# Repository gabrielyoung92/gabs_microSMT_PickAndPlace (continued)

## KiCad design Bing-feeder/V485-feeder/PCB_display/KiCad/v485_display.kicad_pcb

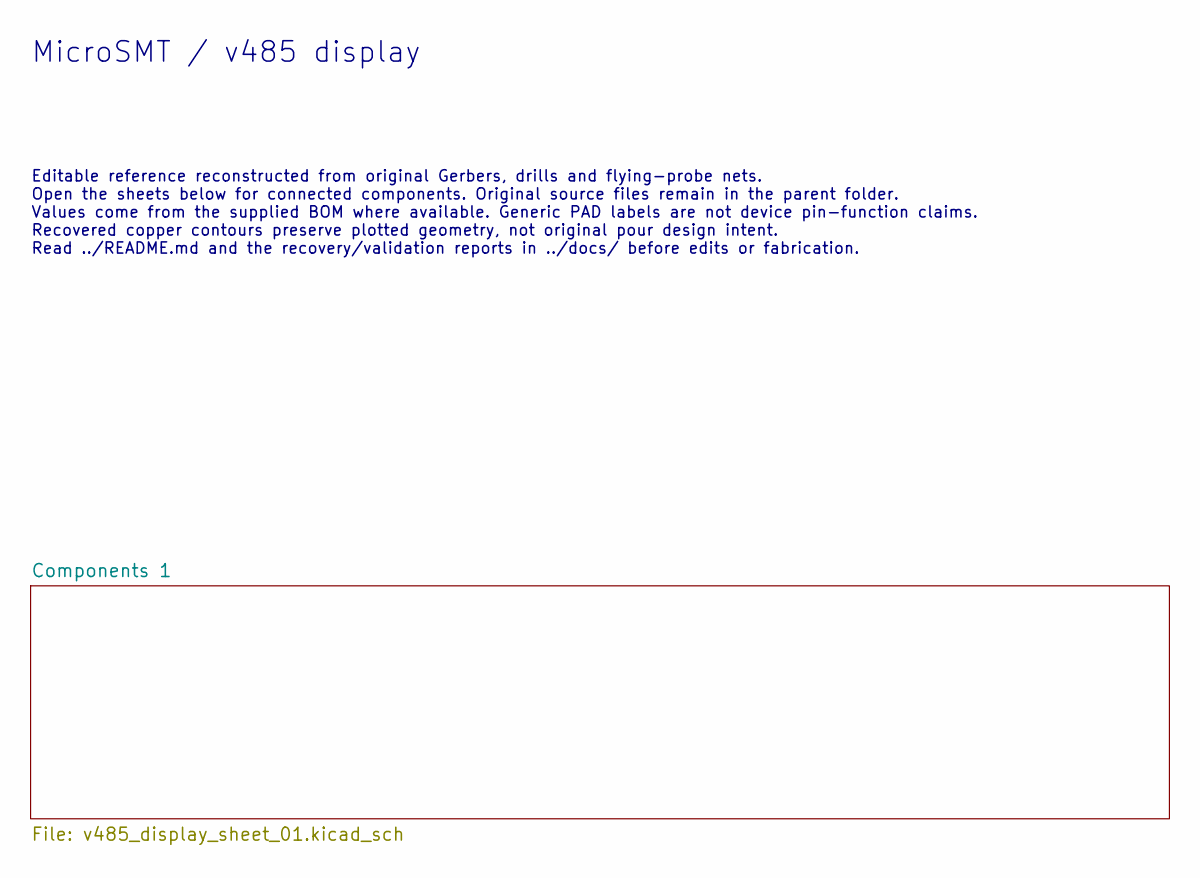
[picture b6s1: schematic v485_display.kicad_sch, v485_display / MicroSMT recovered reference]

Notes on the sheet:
MicroSMT / v485 display
Editable reference reconstructed from original Gerbers, drills and flying-probe nets. Open the sheets below for connected components. Original source files remain in the parent folder. Values come from the supplied BOM where available. Generic PAD labels are not device pin-function claims. Recovere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

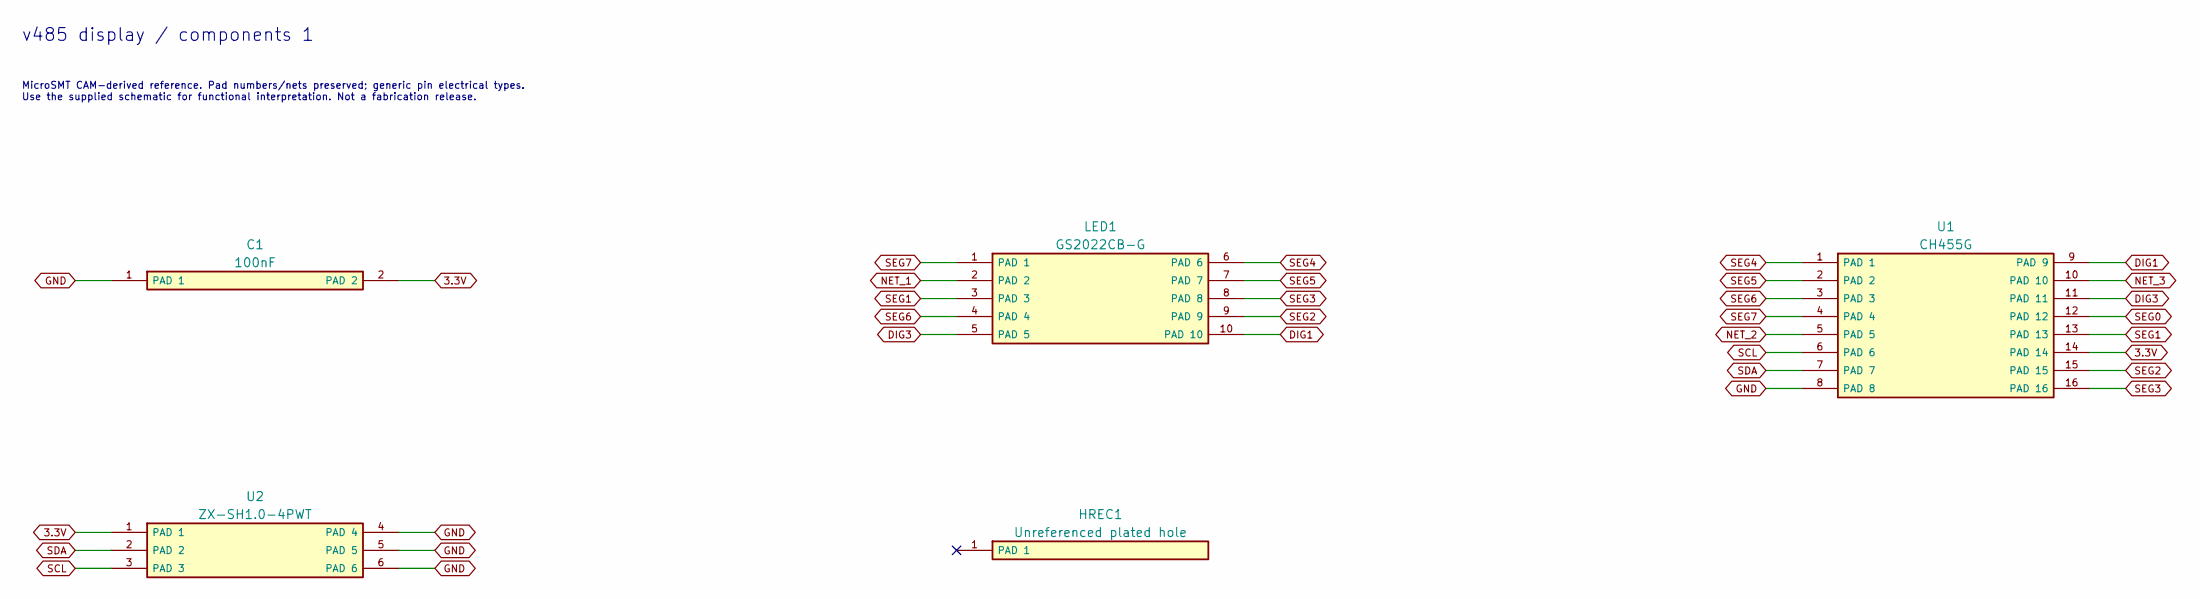
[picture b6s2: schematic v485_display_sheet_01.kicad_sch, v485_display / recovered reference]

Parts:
C1: 100nF; SMD_2_bdaf68bf10
HREC1: Unreferenced plated hole; PTH_1_abea3bc72b
LED1: GS2022CB-G; SMD_10_20c6b414ba
U1: CH455G; SMD_16_61719ae6d4
U2: ZX-SH1.0-4PWT; SMD_6_bf757f6bd6

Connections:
3.3V: C1.2 (PAD 2), U1.14 (PAD 14), U2.1 (PAD 1)
DIG1: LED1.10 (PAD 10), U1.9 (PAD 9)
DIG3: LED1.5 (PAD 5), U1.11 (PAD 11)
GND: C1.1 (PAD 1), U1.8 (PAD 8), U2.4 (PAD 4), U2.5 (PAD 5), U2.6 (PAD 6)
NET_1: LED1.2 (PAD 2)
NET_2: U1.5 (PAD 5)
NET_3: U1.10 (PAD 10)
SCL: U1.6 (PAD 6), U2.3 (PAD 3)
SDA: U1.7 (PAD 7), U2.2 (PAD 2)
SEG0: U1.12 (PAD 12)
SEG1: LED1.3 (PAD 3), U1.13 (PAD 13)
SEG2: LED1.9 (PAD 9), U1.15 (PAD 15)
SEG3: LED1.8 (PAD 8), U1.16 (PAD 16)
SEG4: LED1.6 (PAD 6), U1.1 (PAD 1)
SEG5: LED1.7 (PAD 7), U1.2 (PAD 2)
SEG6: LED1.4 (PAD 4), U1.3 (PAD 3)
SEG7: LED1.1 (PAD 1), U1.4 (PAD 4)

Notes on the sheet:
v485 display / components 1
MicroSMT CAM-derived reference. Pad numbers/nets preserved; generic pin electrical types. Use the supplied schematic for functional interpretation. Not a fabrication release.

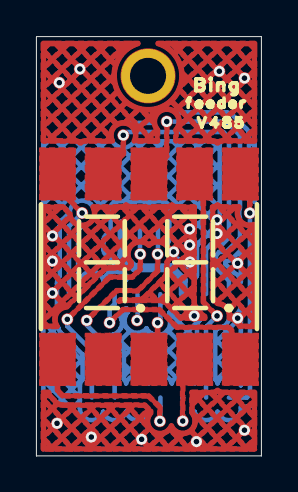
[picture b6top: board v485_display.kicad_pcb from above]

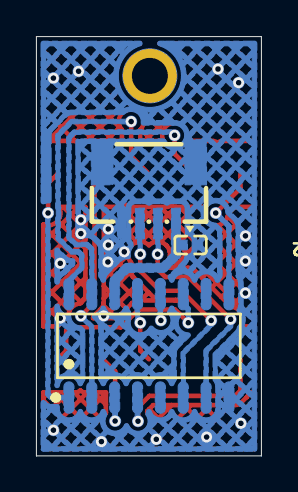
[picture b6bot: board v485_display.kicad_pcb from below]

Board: 2 copper layers, 12.5 x 23.3 mm, 5 parts (3 on the bottom side), 13 nets.

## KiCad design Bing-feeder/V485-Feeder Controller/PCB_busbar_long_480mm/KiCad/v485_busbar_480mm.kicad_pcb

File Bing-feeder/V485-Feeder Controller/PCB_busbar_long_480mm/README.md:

# V485 busbar — 480 mm

> Designs and original files by [MicroSMT](https://github.com/microsmt/Bing-feeder). [Credits and local changes](../../../CREDITS.md).

[Back to collection](../README.md)

Gerbers, editable KiCad files and previews are below.

## KiCad files

Open `.kicad_pro` in **KiCad 10**. Keep the whole `KiCad/` folder together; it contains the local libraries.

The schematics show pad numbers and connections. Use the supplied schematic for pin functions. Review the reported ERC/DRC findings before making a board.

| Project | Open in KiCad | Supporting reports |
| --- | --- | --- |
| V485 480 mm busbar | [v485_busbar_480mm.kicad_pro](KiCad/v485_busbar_480mm.kicad_pro) | [Recovery](docs/recovery.json) · [Validation](docs/validation.json) |

[Recovery details](docs/KICAD_RECOVERY.md) · [Method and editing limits](../../../tools/kicad/RECOVERY_NOTES.md)

## Original board views

[Download Gerber ZIP](Gerber_PCB1_2026-10-09.zip)

<table>
<tr>
<td align="center"><br><sub>Top</sub></td>
<td align="center"><br><sub>Bottom</sub></td>
<td align="center"><br><sub>Top-side isometric</sub></td>
</tr>
</table>

## Assembly notes

MicroSMT specifies **two 480 mm busbars per PNP machine**: one at the front and one at the back.

Gerber previews use display colours and an assumed 1.6 mm thickness; use source data for manufacturing dimensions.

## KiCad previews

KiCad reconstruction views; source Gerber views are above.

### V485 480 mm busbar

<table>
<tr>
<td align="center"><br><sub>Recovered schematic</sub></td>
<td align="center"><br><sub>Recovered PCB top</sub></td>
<td align="center"><br><sub>Recovered PCB bottom</sub></td>
</tr>
</table>

[Sheet overview](photos/kicad-v485_busbar_480mm-overview.jpg) · [Components 1](photos/kicad-v485_busbar_480mm-sheet-01.jpg)

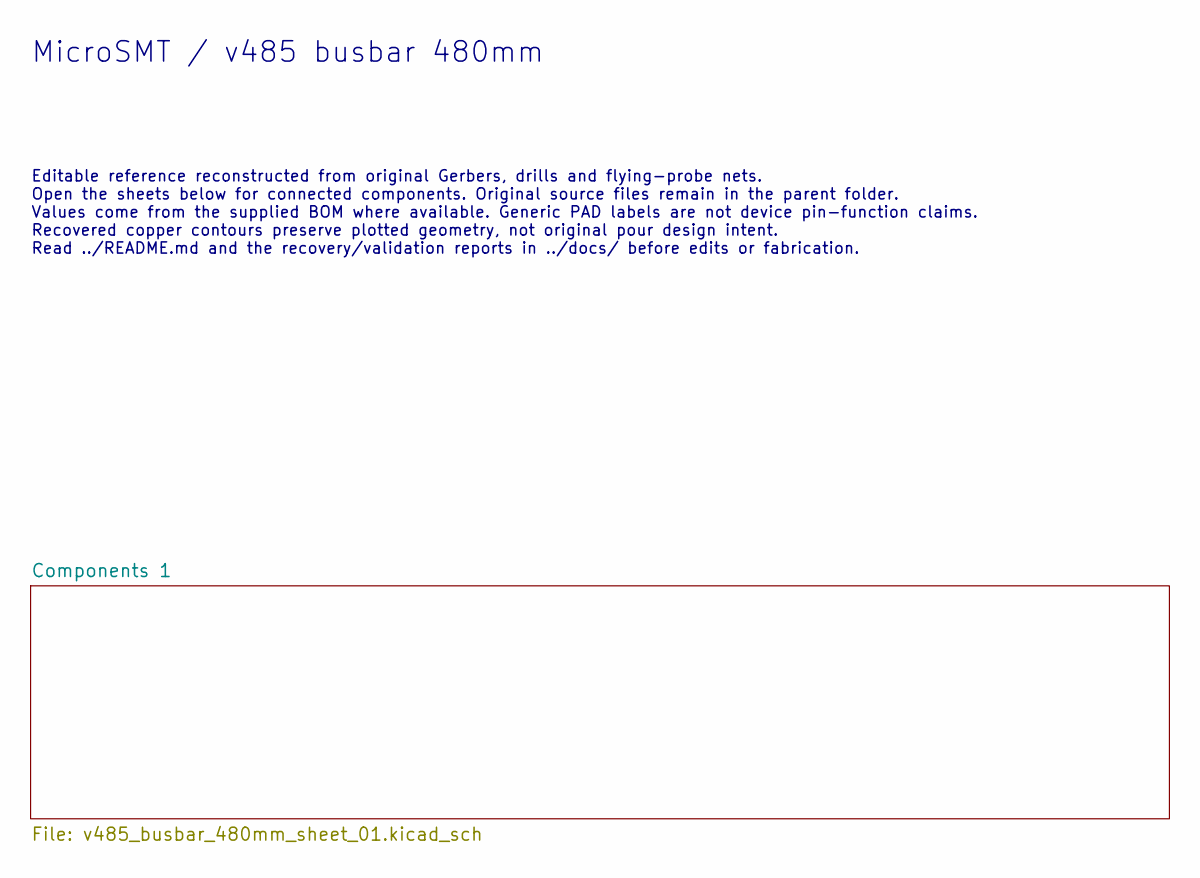
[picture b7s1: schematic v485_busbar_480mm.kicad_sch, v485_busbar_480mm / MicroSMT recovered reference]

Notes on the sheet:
MicroSMT / v485 busbar 480mm
Editable reference reconstructed from original Gerbers, drills and flying-probe nets. Open the sheets below for connected components. Original source files remain in the parent folder. Values come from the supplied BOM where available. Generic PAD labels are not device pin-function claims. Recovere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

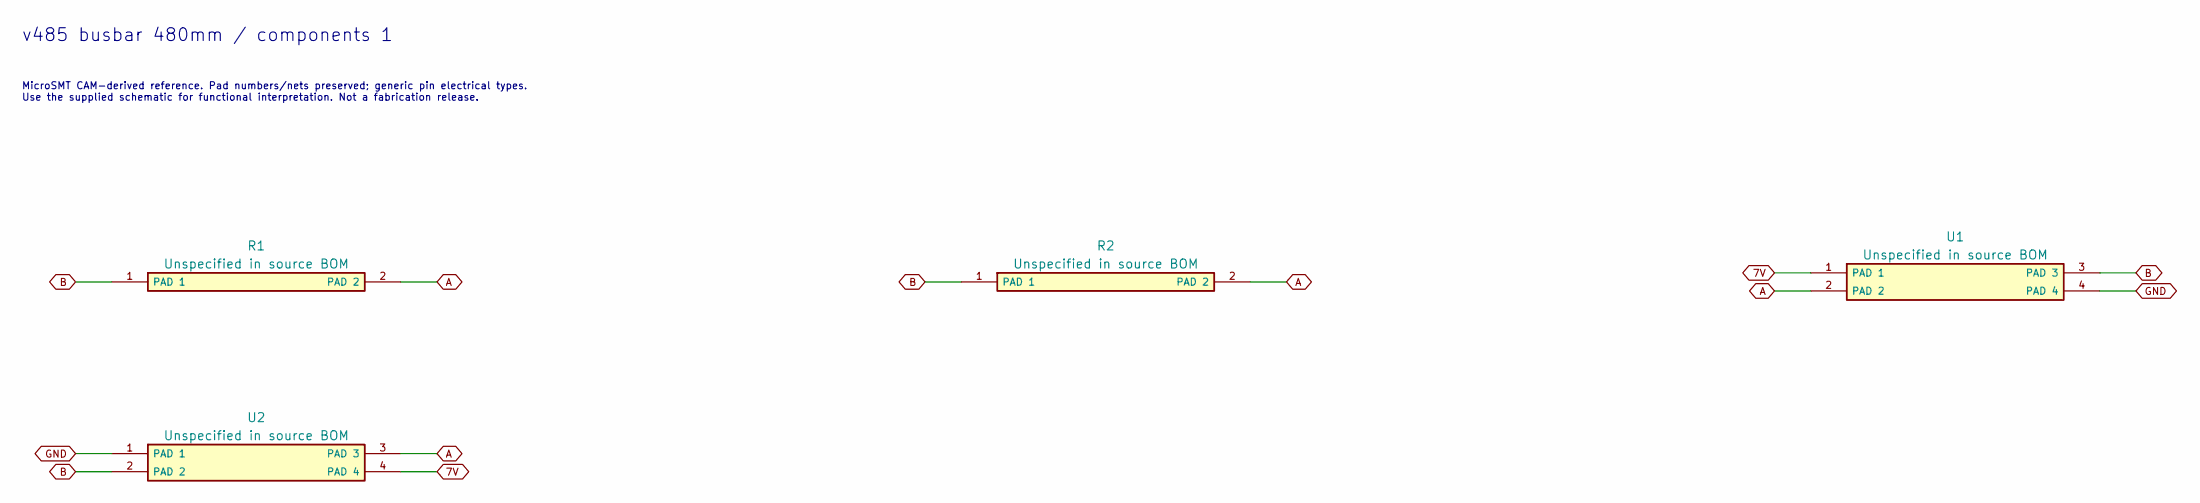
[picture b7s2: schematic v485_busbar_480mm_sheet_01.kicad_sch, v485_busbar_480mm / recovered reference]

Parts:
R1, R2: Unspecified in source BOM; SMD_2_fef7677169
U1: Unspecified in source BOM; PTH_4_06e8961db4
U2: Unspecified in source BOM; PTH_4_6cc8fbf6c8

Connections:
7V: U1.1 (PAD 1), U2.4 (PAD 4)
A: R1.2 (PAD 2), R2.2 (PAD 2), U1.2 (PAD 2), U2.3 (PAD 3)
B: R1.1 (PAD 1), R2.1 (PAD 1), U1.3 (PAD 3), U2.2 (PAD 2)
GND: U1.4 (PAD 4), U2.1 (PAD 1)

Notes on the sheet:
v485 busbar 480mm / components 1
MicroSMT CAM-derived reference. Pad numbers/nets preserved; generic pin electrical types. Use the supplied schematic for functional interpretation. Not a fabrication release.

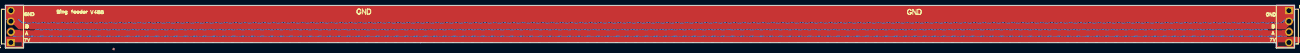
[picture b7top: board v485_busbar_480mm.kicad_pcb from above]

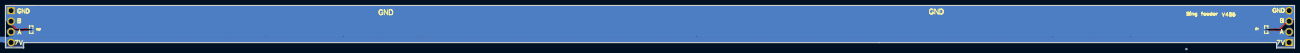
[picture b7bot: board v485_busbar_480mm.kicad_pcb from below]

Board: 2 copper layers, 480.0 x 15.8 mm, 4 parts (2 on the bottom side), 4 nets.

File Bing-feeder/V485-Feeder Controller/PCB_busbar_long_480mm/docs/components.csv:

Reference,Value,Recovered footprint,Pad count,Inferred reference
R1,Unspecified in source BOM,MicroSMT_v485_busbar_480mm:SMD_2_fef7677169,2,False
R2,Unspecified in source BOM,MicroSMT_v485_busbar_480mm:SMD_2_fef7677169,2,False
U1,Unspecified in source BOM,MicroSMT_v485_busbar_480mm:PTH_4_06e8961db4,4,False
U2,Unspecified in source BOM,MicroSMT_v485_busbar_480mm:PTH_4_6cc8fbf6c8,4,False

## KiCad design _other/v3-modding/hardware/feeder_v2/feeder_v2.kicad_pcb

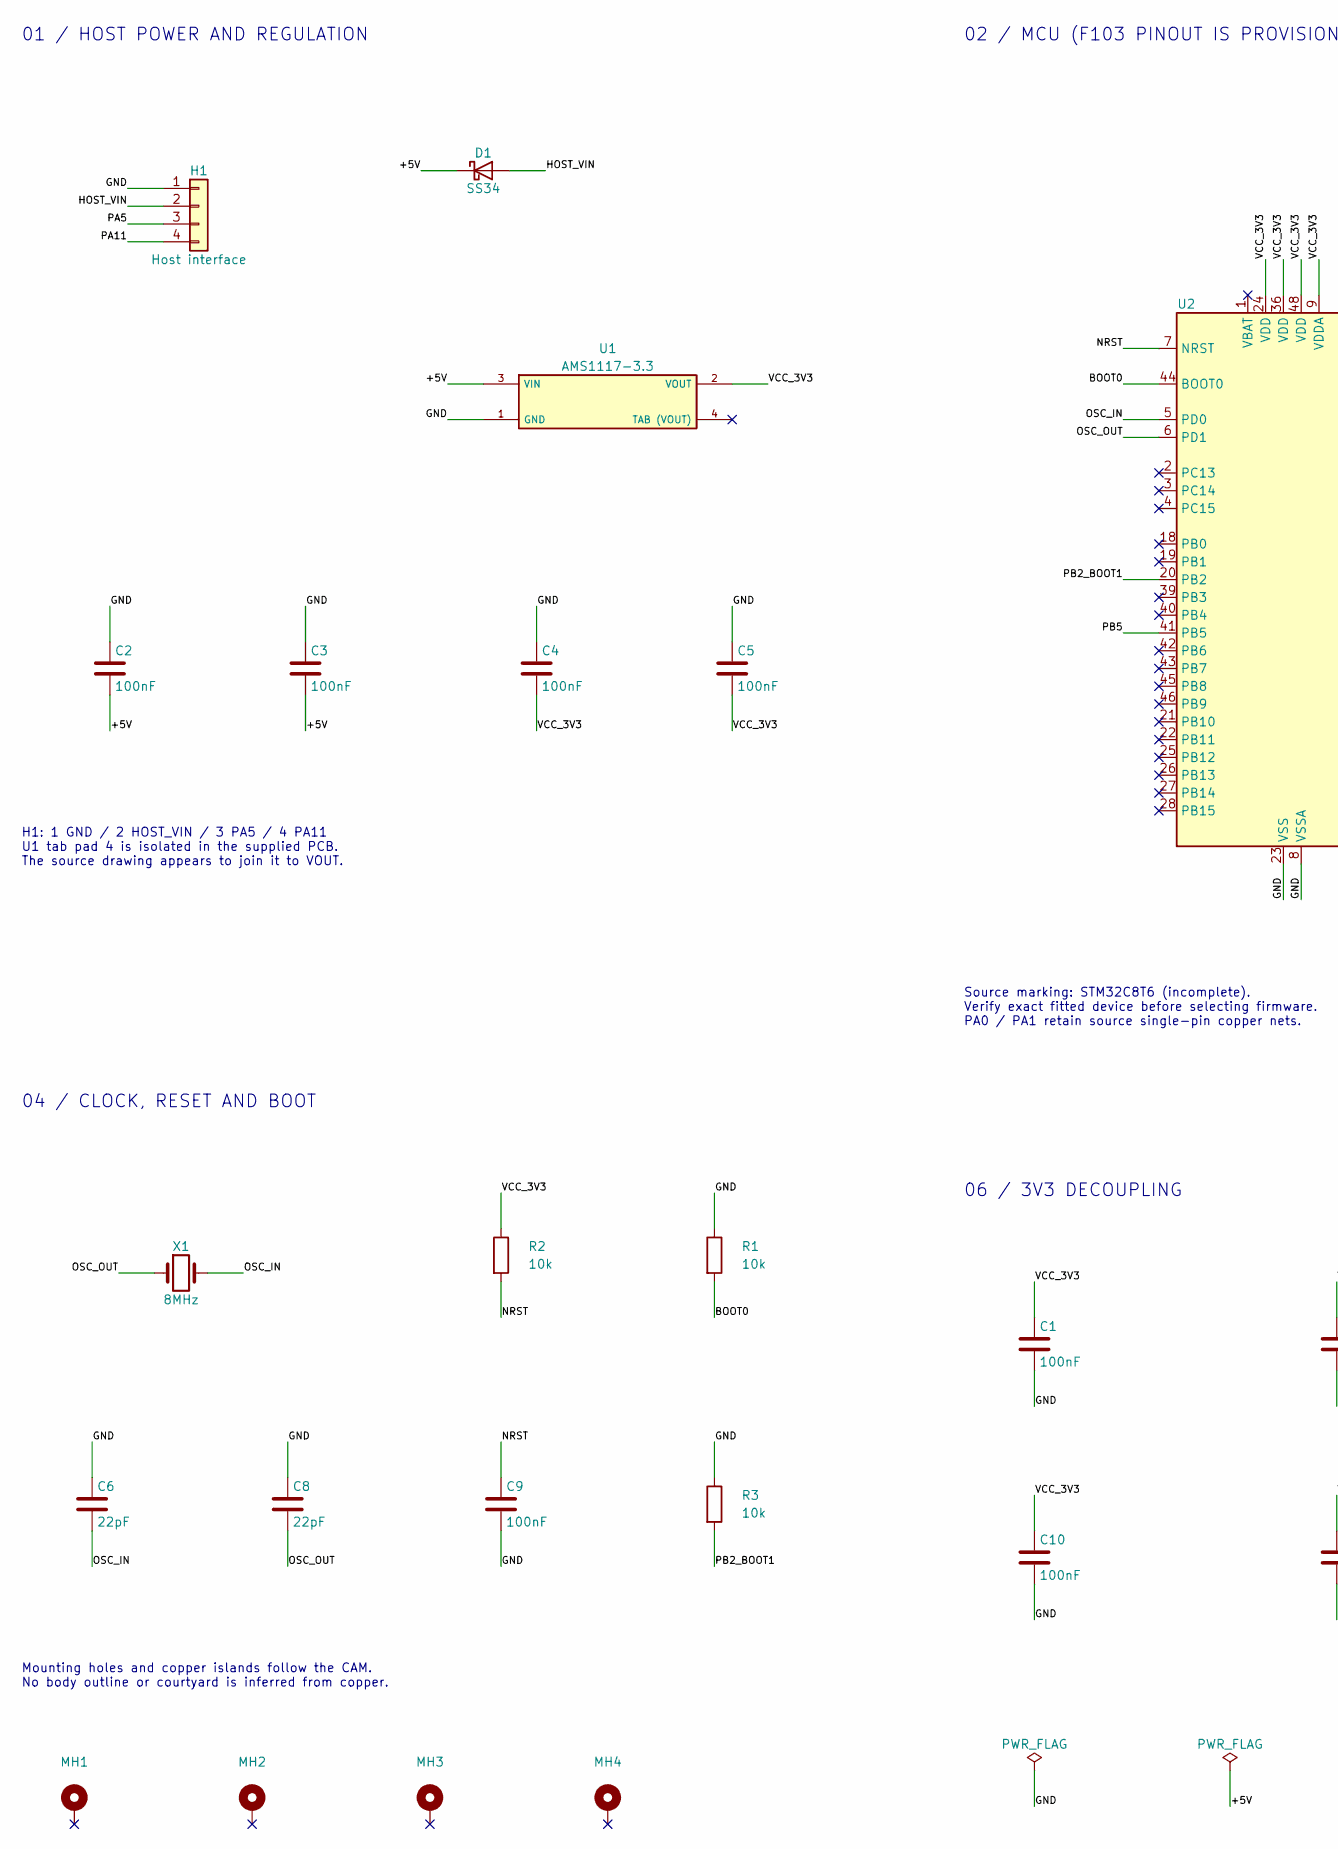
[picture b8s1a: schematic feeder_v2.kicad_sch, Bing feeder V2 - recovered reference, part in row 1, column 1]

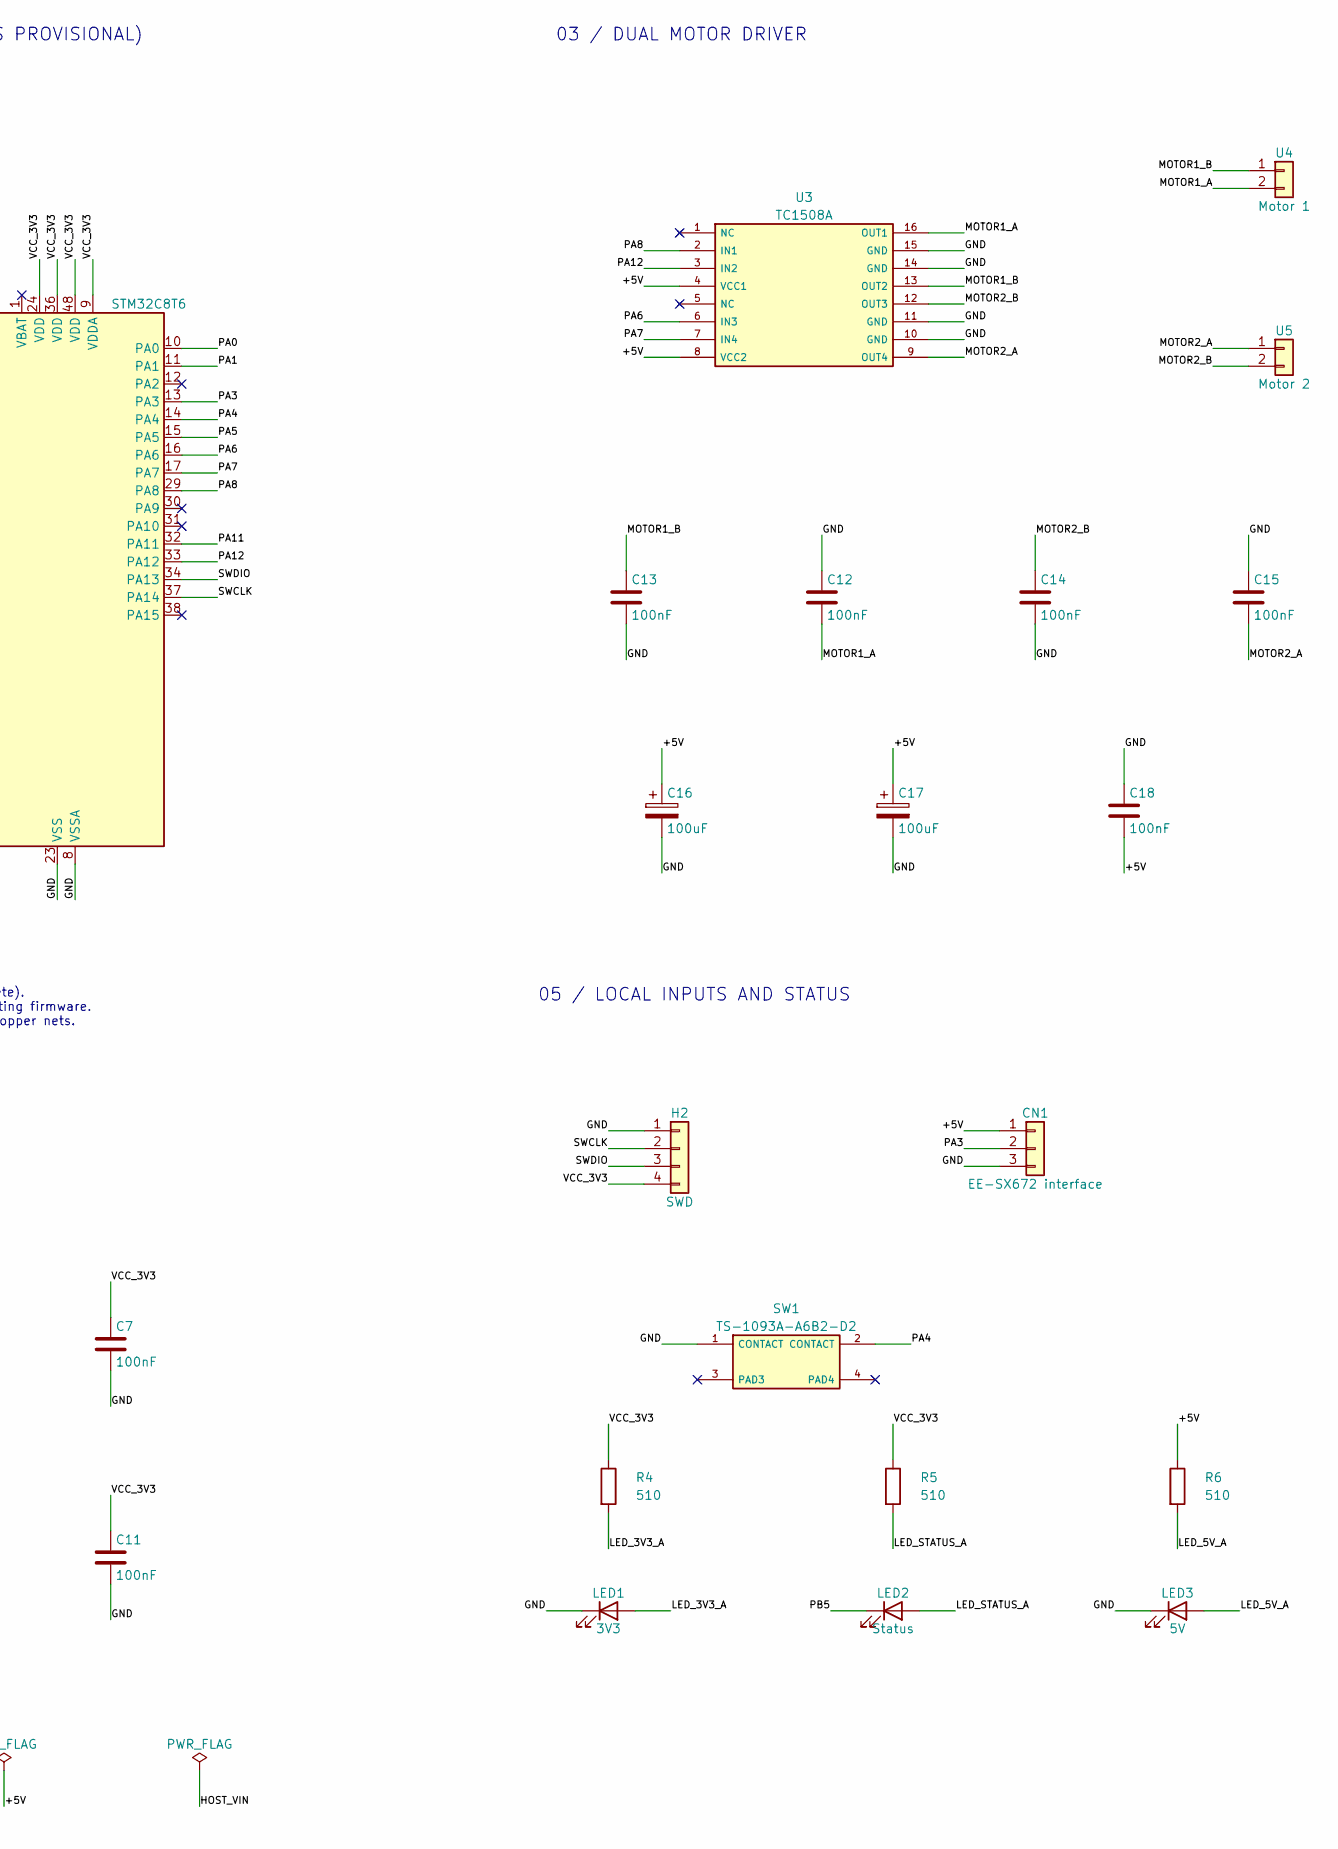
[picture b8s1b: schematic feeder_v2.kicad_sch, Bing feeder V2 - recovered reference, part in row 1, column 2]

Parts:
C1, C4, C5, C9, C10: 100nF; SMD_2_4654a48235
C2, C11: 100nF; SMD_2_6acc588369
C3: 100nF; SMD_2_2eba8715d4
C6: 22pF; SMD_2_6acc588369
C7: 100nF; SMD_2_d7f3dab159
C8: 22pF; SMD_2_d7f3dab159
C12, C13, C15: 100nF; SMD_2_ea9585d00e
C14: 100nF; SMD_2_73e6f4f0fe
C16: 100uF; SMD_2_ec123379e2
C17: 100uF; SMD_2_6e07a3e01f
C18: 100nF; SMD_2_9b88676047
CN1: EE-SX672 interface; PTH_3_4a05049ecf
D1: SS34; SMD_2_2eb83b068d
H1: Host interface; PTH_4_349c8e8e96
H2: SWD; PTH_4_b36c63a0fc
LED1: 3V3; SMD_2_d3d32b5ec5
LED2: Status; SMD_2_90d08f57e1
LED3: 5V; SMD_2_4c3ddea3bf
MH1, MH2, MH3, MH4: Plated mounting hole 2.5mm; PTH_1_75dcf4be66
R1: 10k; SMD_2_0ab8a8e8a3
R2, R3: 10k; SMD_2_d2af6b9a79
R4: 510; SMD_2_a94b28ce2e
R5: 510; SMD_2_b14ba15cf3
R6: 510; SMD_2_d2af6b9a79
SW1: TS-1093A-A6B2-D2; PTH_4_230f0c19bc
U1: AMS1117-3.3; SMD_4_f5cc46188f
U2: STM32C8T6; SMD_48_5916ba93e4
U3: TC1508A; SMD_16_ae7b02a39a
U4: Motor 1; PTH_2_ae613bcbab
U5: Motor 2; PTH_2_ae613bcbab
X1: 8MHz; PTH_2_5813266c9b

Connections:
/+5V: C2.2, C3.2, C16.1, C17.1, C18.2, CN1.1, D1.1 (K), R6.1, U1.3 (VIN), U3.4 (VCC1), U3.8 (VCC2)
/BOOT0: R1.2, U2.44 (BOOT0)
/GND: C1.2, C2.1, C3.1, C4.1, C5.1, C6.1, C7.2, C8.1, C9.2, C10.2, C11.2, C12.1, C13.2, C14.2, C15.1, C16.2, C17.2, C18.1, CN1.3, H1.1, H2.1, LED1.1 (K), LED3.1 (K), R1.1, R3.1, SW1.1 (CONTACT), U1.1 (GND), U2.8 (VSSA), U2.23 (VSS), U2.35 (VSS), U2.47 (VSS), U3.10 (GND), U3.11 (GND), U3.14 (GND), U3.15 (GND)
/HOST_VIN: D1.2 (A), H1.2
/LED_3V3_A: LED1.2 (A), R4.2
/LED_5V_A: LED3.2 (A), R6.2
/LED_STATUS_A: LED2.2 (A), R5.2
/MOTOR1_A: C12.2, U3.16 (OUT1), U4.2
/MOTOR1_B: C13.1, U3.13 (OUT2), U4.1
/MOTOR2_A: C15.2, U3.9 (OUT4), U5.1
/MOTOR2_B: C14.1, U3.12 (OUT3), U5.2
/NRST: C9.1, R2.2, U2.7 (NRST)
/OSC_IN: C6.2, U2.5 (PD0), X1.2
/OSC_OUT: C8.2, U2.6 (PD1), X1.1
/PA0: U2.10 (PA0)
/PA1: U2.11 (PA1)
/PA3: CN1.2, U2.13 (PA3)
/PA4: SW1.2 (CONTACT), U2.14 (PA4)
/PA5: H1.3, U2.15 (PA5)
/PA6: U2.16 (PA6), U3.6 (IN3)
/PA7: U2.17 (PA7), U3.7 (IN4)
/PA8: U2.29 (PA8), U3.2 (IN1)
/PA11: H1.4, U2.32 (PA11)
/PA12: U2.33 (PA12), U3.3 (IN2)
/PB2_BOOT1: R3.2, U2.20 (PB2)
/PB5: LED2.1 (K), U2.41 (PB5)
/SWCLK: H2.2, U2.37 (PA14)
/SWDIO: H2.3, U2.34 (PA13)
/VCC_3V3: C1.1, C4.2, C5.2, C7.1, C10.1, C11.1, H2.4, R2.1, R4.1, R5.1, U1.2 (VOUT), U2.9 (VDDA), U2.24 (VDD), U2.36 (VDD), U2.48 (VDD)

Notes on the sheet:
01 / HOST POWER AND REGULATION
H1: 1 GND / 2 HOST_VIN / 3 PA5 / 4 PA11 U1 tab pad 4 is isolated in the supplied PCB. The source drawing appears to join it to VOUT.
02 / MCU (F103 PINOUT IS PROVISIONAL)
Source marking: STM32C8T6 (incomplete). Verify exact fitted device before selecting firmware. PA0 / PA1 retain source single-pin copper nets.
03 / DUAL MOTOR DRIVER
04 / CLOCK, RESET AND BOOT
05 / LOCAL INPUTS AND STATUS
06 / 3V3 DECOUPLING
Mounting holes and copper islands follow the CAM. No body outline or courtyard is inferred from copper.

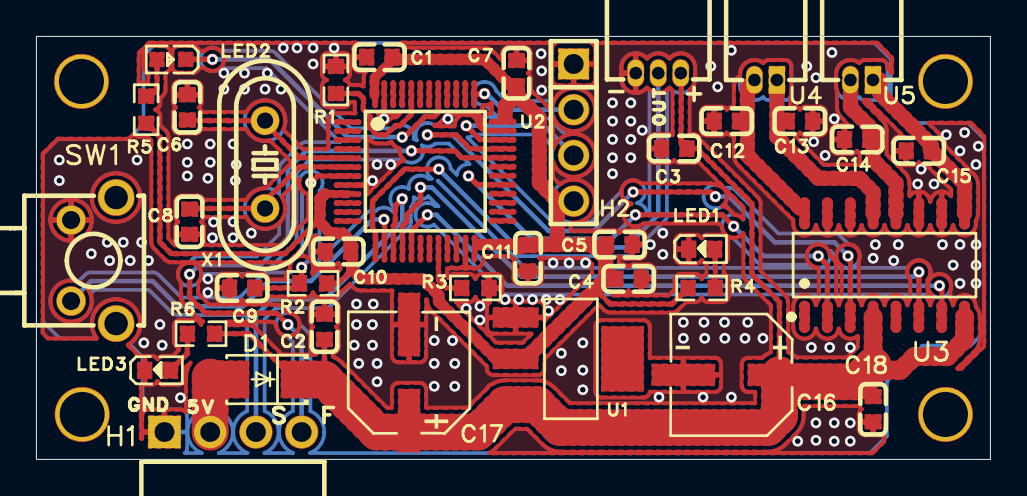
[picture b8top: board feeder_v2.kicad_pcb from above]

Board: 2 copper layers, 53.0 x 23.5 mm, 42 parts (0 on the bottom side), 27 nets.

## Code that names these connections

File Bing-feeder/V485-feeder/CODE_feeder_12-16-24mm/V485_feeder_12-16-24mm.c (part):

// ============================================================
//  STM32F103 Slave (Feeder) Firmware V26
//  Features:
//    1. Encoder PB6 trigger (rising edge), PA3 count (rising edge),
//       motor stops at motorCount
//    2. Buttons PA2/PA4 short press to adjust address/count,
//       long press to switch mode
//    3. RS485 receive N<addr> F<cnt>, execute only when addr==currentAddr
//    4. 24C02 saves address and count
//    5. CH455 digital tube display
//    6. LED indication: on while motor runs, off when stopped;
//       fast flash on button/command
//    7. Group 1 (PA6/PA7): controlled start/stop
//       Group 2 (PA8/PA12): always running, PA12=1, PA8=0
//  Version: V26
// ============================================================

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static volatile uint8_t mode = MODE_NORMAL;

static volatile uint8_t  encoderMute = 0;      // Only used for RS485 echo prevention
static volatile uint8_t  pa3TriggerCount = 0;  // PA3 pulse count
static volatile uint8_t  pa3CountEnabled = 0;  // Real busy flag: motor is running
static volatile uint32_t pa4TriggerMute = 0;   // PA2 manual trigger debounce

static volatile uint8_t  rs485TempCount = 0;   // Count brought by RS485 command
static volatile uint8_t  motorCount = 0;       // Steps the motor needs to run this time
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    uint8_t  long_trig;
    uint8_t  ignoreShort;
} KEY_Typedef;
static KEY_Typedef key_inc;                    // PA2 button
static KEY_Typedef key_dec;                    // PA4 button

// RS485 ring receive buffer
static volatile uint8_t  rs485RxBuf[RS485_RX_BUF_SIZE];
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static void USART1_SendString(const char* str);
static void USART1_Init(void);
static void ProcessRS485(void);
static void Motor2_AlwaysRun(void);            // Keep PA8/PA12 group running

// ================== 24C02 Software I2C ==================
#define SCL_HIGH()  GPIO_SetBits(I2C_PORT, I2C_SCL_PIN)
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
// Key scan: state machine, supports short press/long press
static void KeyScan(void) {
    // ---------- PA4 (key_dec) ----------
    uint8_t inc_pin = GPIO_ReadInputDataBit(GPIOA, GPIO_Pin_4);
    switch (key_dec.state) {
        case 0U:
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            break;
    }

    // ---------- PA2 (key_inc) ----------
    uint8_t dec_pin = GPIO_ReadInputDataBit(GPIOA, GPIO_Pin_2);
    switch (key_inc.state) {
        case 0U:
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            break;
    }

    // ---------- Short press handling: PA4 ----------
    if (key_dec.short_trig) {
        key_dec.short_trig = 0U;
        if (key_dec.ignoreShort) {
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        }
    }

    // ---------- Short press handling: PA2 ----------
    if (key_inc.short_trig) {
        key_inc.short_trig = 0U;
        if (key_inc.ignoreShort) {
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                    RefreshDisplay();
                }
            } else {
                // Normal mode: PA2 short press = manually trigger motor once
                if (pa4TriggerMute == 0 && pa3CountEnabled == 0) {
                    rs485TempCount = 0;     // 0 means use currentCount
                    Motor_Start();
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}

// ================== Motor ==================
// Keep PA8/PA12 group running: PA12 = HIGH, PA8 = LOW
static void Motor2_AlwaysRun(void) {
    GPIO_SetBits(GPIOA, GPIO_Pin_12);     // PA12 = 1
    GPIO_ResetBits(GPIOA, GPIO_Pin_8);    // PA8  = 0
}

static void Motor_Start(void) {
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        RefreshDisplay();
    }

    // ---- Group 1 (PA6/PA7): controlled ----
    GPIO_SetBits(GPIOA, GPIO_Pin_6);
    GPIO_ResetBits(GPIOA, GPIO_Pin_7);

    // ---- Group 2 (PA8/PA12): always running ----
    Motor2_AlwaysRun();

    LED_ON();
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}

static void Motor_Stop(void) {
    // ---- Group 1 (PA6/PA7): stop ----
    GPIO_SetBits(GPIOA, GPIO_Pin_6 | GPIO_Pin_7);

    // ---- Group 2 (PA8/PA12): always running ----
    Motor2_AlwaysRun();

    LED_OFF();
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    GPIO_InitStruct.GPIO_Mode  = GPIO_Mode_IN_FLOATING;
    GPIO_Init(GPIOA, &GPIO_InitStruct);

    // PA1 = DE/RE
    GPIO_InitStruct.GPIO_Pin   = GPIO_Pin_1;
    GPIO_InitStruct.GPIO_Mode  = GPIO_Mode_Out_PP;
    GPIO_InitStruct.GPIO_Speed = GPIO_Speed_50MHz;
    GPIO_Init(GPIOA, &GPIO_InitStruct);
    RS485_SetTransmit(0);

    // PB5 = LED
    GPIO_InitStruct.GPIO_Pin   = GPIO_Pin_5;
    GPIO_InitStruct.GPIO_Mode  = GPIO_Mode_Out_PP;
    GPIO_InitStruct.GPIO_Speed = GPIO_Speed_50MHz;
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    RCC_APB2PeriphClockCmd(RCC_APB2Periph_GPIOA | RCC_APB2Periph_AFIO, ENABLE);
    RCC_APB2PeriphClockCmd(RCC_APB2Periph_GPIOB | RCC_APB2Periph_AFIO, ENABLE);

    // PA6 PA7 PA8 PA12 output (motor control)
    GPIO_InitStructure.GPIO_Pin   = GPIO_Pin_6 | GPIO_Pin_7 | GPIO_Pin_8 | GPIO_Pin_12;
    GPIO_InitStructure.GPIO_Mode  = GPIO_Mode_Out_PP;
    GPIO_InitStructure.GPIO_Speed = GPIO_Speed_50MHz;
    GPIO_Init(GPIOA, &GPIO_InitStructure);

    // PB5 LED output
    GPIO_InitStructure.GPIO_Pin   = GPIO_Pin_5;
    GPIO_InitStructure.GPIO_Mode  = GPIO_Mode_Out_PP;
    GPIO_InitStructure.GPIO_Speed = GPIO_Speed_50MHz;
    GPIO_Init(GPIOB, &GPIO_InitStructure);

    // PA3 input (encoder pulse)
    GPIO_InitStructure.GPIO_Pin  = GPIO_Pin_3;
    GPIO_InitStructure.GPIO_Mode = GPIO_Mode_IN_FLOATING;
    GPIO_Init(GPIOA, &GPIO_InitStructure);

    // PB6 input (encoder trigger)
    GPIO_InitStructure.GPIO_Pin  = GPIO_Pin_6;
    GPIO_InitStructure.GPIO_Mode = GPIO_Mode_IN_FLOATING;
    GPIO_Init(GPIOB, &GPIO_InitStructure);

    // PA2 PA4 input (buttons)
    GPIO_InitStructure.GPIO_Pin  = GPIO_Pin_2 | GPIO_Pin_4;
    GPIO_InitStructure.GPIO_Mode = GPIO_Mode_IN_FLOATING;
    GPIO_Init(GPIOA, &GPIO_InitStructure);
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    GPIO_SetBits(GPIOA, GPIO_Pin_6 | GPIO_Pin_7);   // Group 1 idle high
    GPIO_SetBits(GPIOB, GPIO_Pin_5);                // LED off

    // Group 2 (PA8/PA12): always running from power-up
    Motor2_AlwaysRun();
}

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    EXTI_InitTypeDef EXTI_InitStructure;
    NVIC_InitTypeDef NVIC_InitStructure;

    // PB6 -> EXTI6 (encoder trigger)
    GPIO_EXTILineConfig(GPIO_PortSourceGPIOB, GPIO_PinSource6);
    EXTI_InitStructure.EXTI_Line    = EXTI_Line6;
    EXTI_InitStructure.EXTI_Mode    = EXTI_Mode_Interrupt;
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    NVIC_InitStructure.NVIC_IRQChannelCmd                = ENABLE;
    NVIC_Init(&NVIC_InitStructure);

    // PA3 -> EXTI3 (encoder count)
    GPIO_EXTILineConfig(GPIO_PortSourceGPIOA, GPIO_PinSource3);
    EXTI_InitStructure.EXTI_Line    = EXTI_Line3;
    EXTI_InitStructure.EXTI_Trigger = EXTI_Trigger_Rising;
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
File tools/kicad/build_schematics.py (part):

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    place('D1','D_Schottky',88.9,40.64)
    place('U1','AMS1117_4pad',106.68,73.66)
    for ref,x in [('C2',35.56),('C3',63.5),('C4',96.52),('C5',124.46)]:place(ref,'C',x,111.76)
    sh.text('H1: 1 GND / 2 HOST_VIN / 3 PA5 / 4 PA11\nU1 tab pad 4 is isolated in the supplied PCB.\nThe source drawing appears to join it to VOUT.',22.86,134.62)
    sh.section('02 / MCU (F103 PINOUT IS PROVISIONAL)',157.48,20.32)
    place('U2','STM32F103C8Tx',203.2,99.06)
    sh.text('Source marking: STM32C8T6 (incomplete).\nVerify exact fitted device before selecting firmware.\nPA0 / PA1 retain source single-pin copper nets.',157.48,157.48)
    sh.section('03 / DUAL MOTOR DRIVER',274.32,20.32)
    place('U3','TC1508A',309.88,58.42)
    place('U4','Conn_01x02',378.46,40.64);place('U5','Conn_01x02',378.46,66.04)
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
